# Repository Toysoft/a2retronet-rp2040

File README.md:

# A2retroNET RP2040

_Directly connecting the [Raspberry Pi RP2040](https://www.raspberrypi.com/products/rp2040/) to the Apple II slot bus_

[Demo Program](demo/README.md)

This is a HW implementation of Oliver Schmidt's recommended designs.

Version 1.4 is the innitial design with 3x 74LVC245 and 1x 74HC08 to prove the concept. However it is obsolete as it does not switch off the Expansion ROM ($C800-$CFFF), which is always available and could cause data bus conlisions if used with other cards that use this memory space.

Version 1.5 switches off the Expansion ROM ($C800-$CFFF) when $CFFF is accessed or when reset is issued, and switches it back on again when the slot memory is accessed (IOSelect).

Version 1.6 combines 3 of the logic chips into a PLD. 74LS08, 74LS133 and 74LS02 are replaced by ATF22V10.

The RPI usage is as follows:

| GPIO    | Usage     |
|:--------|:----------|
| 0       |  UART TX  |
| 1       |  UART RX  |
| 2 - 13  | A0 - A11  |
| 14      | R/W       |
| 15 - 22 | D0 - D7   |
| 26      | ENBL      |
| 27      | IRQ       |
| 28      | RES       |

Version "n" has support for a MicroSD card with **no** ExtROM capability.

The RPI usage of the "n" versions is as follows:

| GPIO    | Usage     |
|:--------|:----------|
| 0       |  SPI RX   |
| 1       |  SPI CSn  |
| 2       |  SPI SCK  |
| 3       |  SPI TX   |
| 4       |  NMI      |
| 5 - 12  | A0 - A7   |
| 13      | DEVSEL    |
| 14      | R/W       |
| 15 - 22 | D0 - D7   |
| 26      | ENBL      |
| 27      |  IRQ      |
| 28      |  RES      |

There is a suggested driver for a ProDOS block device for the "n" version.

However, there is a current need for development of a firmware for the "n" version for the RPI Pico to drive the IO with the A2 and the MicroSD card.

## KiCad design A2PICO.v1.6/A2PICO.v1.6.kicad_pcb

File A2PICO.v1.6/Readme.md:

Version 1.6 combines 3 of the logic chips into a PLD.
74HC08, 74LS133 and 74LS02 are replaced by ATF22V10.

The RPI usage is as follows:

| GPIO    | Usage     |
|:--------|:----------|
| 0       |  UART TX  |
| 1       |  UART RX  |
| 2 - 13  | A0 - A11  |
| 14      | R/W       |
| 15 - 22 | D0 - D7   |
| 26      | ENBL      |
| 27      | IRQ       |
| 28      | RES       |

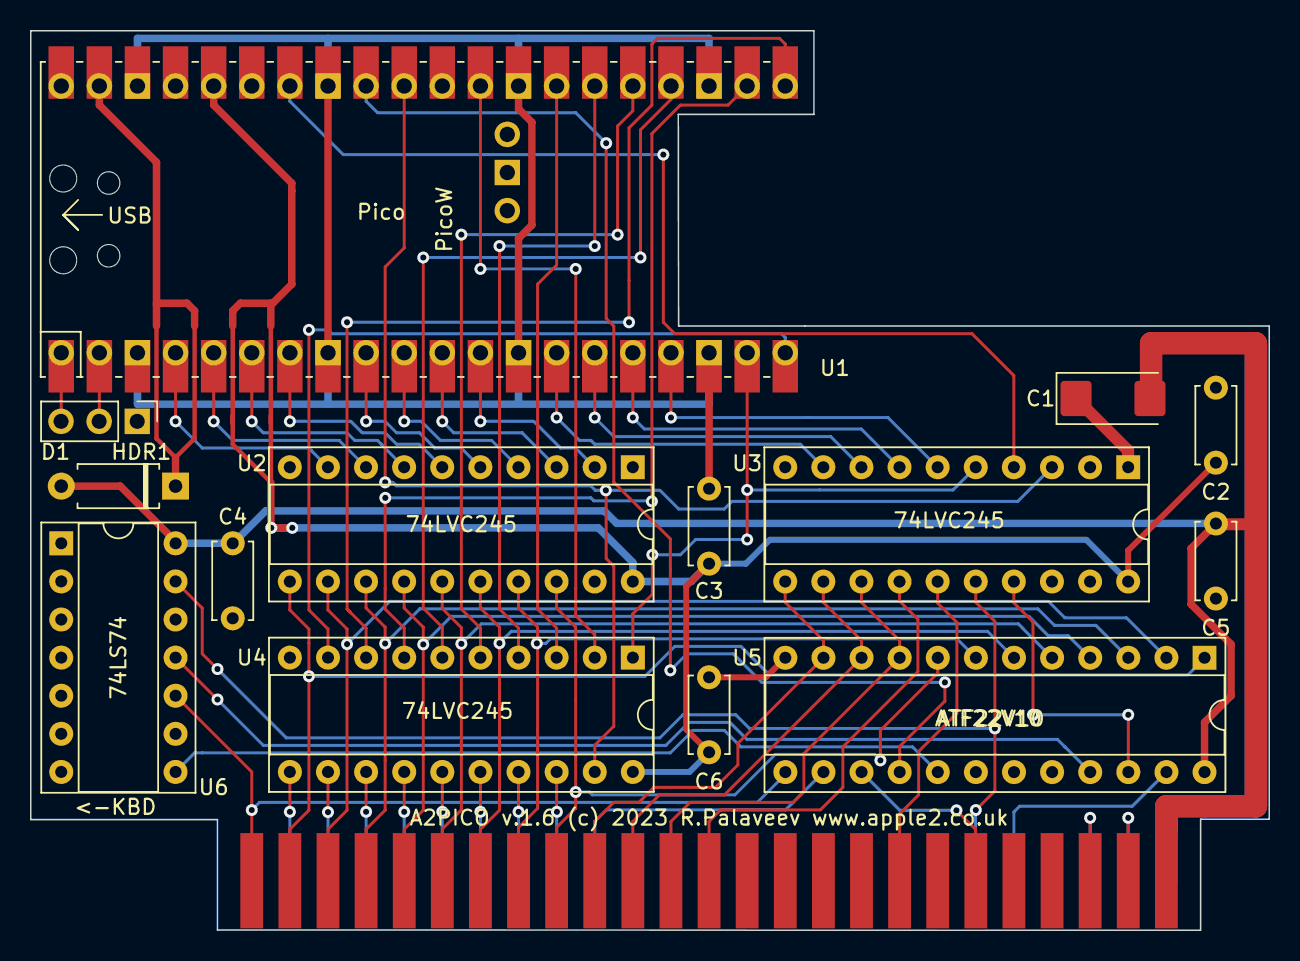
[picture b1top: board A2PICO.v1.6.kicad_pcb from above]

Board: 2 copper layers, 82.5 x 60.0 mm, 14 parts (0 on the bottom side), 4 nets.

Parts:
C1: 220uF; CP_EIA-6032-15_Kemet-U
C2, C3, C4, C5, C6: 100n; C_Disc_D5.0mm_W2.5mm_P5.00mm
D1: D_A-405_P7.62mm_Horizontal
HDR1: PinHeader_1x03_P2.54mm_Vertical
U1: PicoW; RPi_PicoW_SMD_TH
U2, U3, U4: 74LVC245; DIP-20_W7.62mm_Socket
U5: ATF22V10; DIP-24_W7.62mm_Socket
U6: 74LS74; DIP-14_W7.62mm_Socket

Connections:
3.3V: C2.1, C3.1, C6.1, U1.36 (3V3), U2.20, U3.20, U4.20
5V: C1.2, C4.2, C5.2, D1.2, U5.24, U6.14
GND: C1.1, C2.2, C3.2, C4.1, C5.1, C6.2, HDR1.1, U1.3 (GND), U1.8 (GND), U1.13 (GND), U1.18 (GND), U1.23 (GND), U1.28 (GND), U1.33 (AGND), U1.38 (GND), U2.1, U2.10, U2.19, U3.1, U3.10, U3.19, U4.10, U5.12, U6.2, U6.7, U6.12
VSYS: D1.1, U1.39 (VSYS)

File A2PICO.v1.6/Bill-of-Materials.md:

|Qty|Designator|Item|Package|Description|
|---|---|---|---|---|
|1x|C1|6.3V 220uF X5R|0805|Multilayer Ceramic Capacitor|
|9x|C2-C6|50V 100nF X7R|0402|Multilayer Ceramic Capacitor|
|1x|D1|SS14F|SMAF|40V 550mV @ 1A Shottkey Barrier Diode|
|1x|U1|Pico-W|Module|Raspberry Pi Pico or Pico-W module (no pins)|
|3x|U2-U4|SN74LVC245A|PDIP-20|Texas Instruments SN74LVC245A Octal Bus Transceiver With 3-State Outputs|
|1x|U5|ATF22V10C-10PC|PDIP-24|Microchip ATF22V10C PLD|
|1x|U6|SN74LS74|PDIP-14|Dual Positive-Edge-Triggered D Flip-Flops with Pr, Cl and Complementary Outputs|
|1x|HDR1|3-pin Header|HD-3|TH PinHeader_1x03_P2.54mm_Vertical|

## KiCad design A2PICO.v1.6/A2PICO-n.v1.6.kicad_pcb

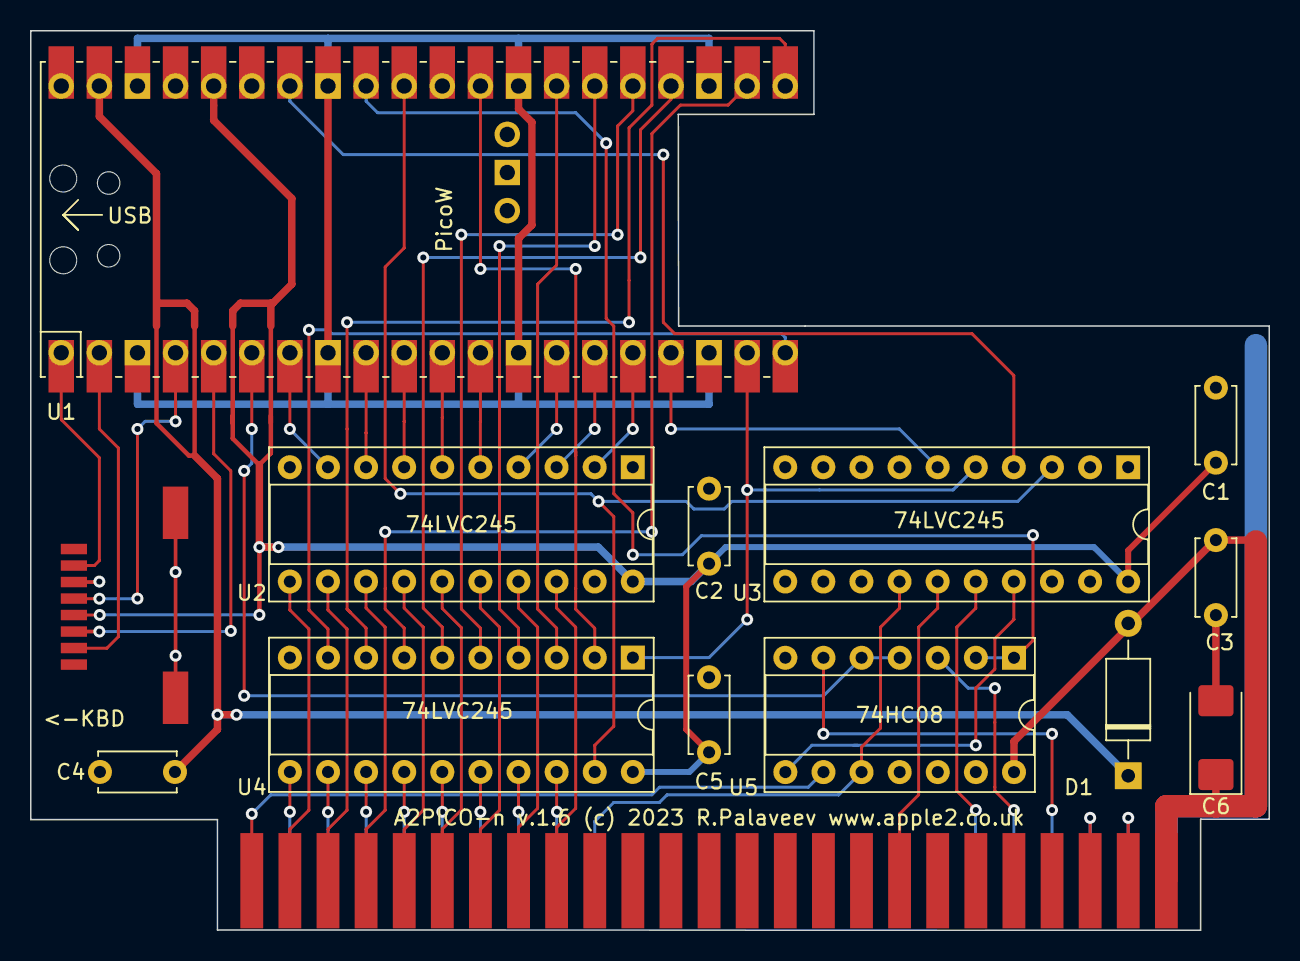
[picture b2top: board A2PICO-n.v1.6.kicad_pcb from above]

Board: 2 copper layers, 82.5 x 60.0 mm, 12 parts (0 on the bottom side), 4 nets.

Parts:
C1, C2, C3, C4, C5: 100n; C_Disc_D5.0mm_W2.5mm_P5.00mm
C6: 220uF; CP_EIA-6032-15_Kemet-U
D1: D_A-405_P10.16mm_Horizontal
U1: PicoW; RPi_PicoW_SMD_TH
U2, U3, U4: 74LVC245; DIP-20_W7.62mm_Socket
U5: 74HC08; DIP-14_W7.62mm_Socket

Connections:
3.3V: C1.1, C2.1, C5.1, U1.36 (3V3), U2.20, U3.20, U4.20
5V: C3.2, C6.1, D1.2, U5.14
GND: C1.2, C2.2, C3.1, C4.1, C5.2, C6.2, U1.3 (GND), U1.8 (GND), U1.13 (GND), U1.18 (GND), U1.23 (GND), U1.28 (GND), U1.33 (AGND), U1.38 (GND), U2.1, U2.10, U2.19, U3.1, U3.10, U3.19, U4.10, U5.7
VSYS: C4.2, D1.1, U1.39 (VSYS)

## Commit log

2023-08-27 Create test
2023-09-20 Rename A2PICO.V1.6-alt.PLD to A2PICO-alt.V1.6.PLD

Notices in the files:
A2PICO.v1.6/A2PICO-n.v1.6.kicad_pcb:
A2PICO-n v.1.6 (c) 2023 R.Palaveev www.apple2.co.uk
A2PICO.v1.6/A2PICO.v1.6.kicad_pcb:
A2PICO v.1.6 (c) 2023 R.Palaveev www.apple2.co.uk
